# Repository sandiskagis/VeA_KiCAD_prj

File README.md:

# VeA_KiCAD_prj
Šī repozitorija paredzēta kursa projektiem

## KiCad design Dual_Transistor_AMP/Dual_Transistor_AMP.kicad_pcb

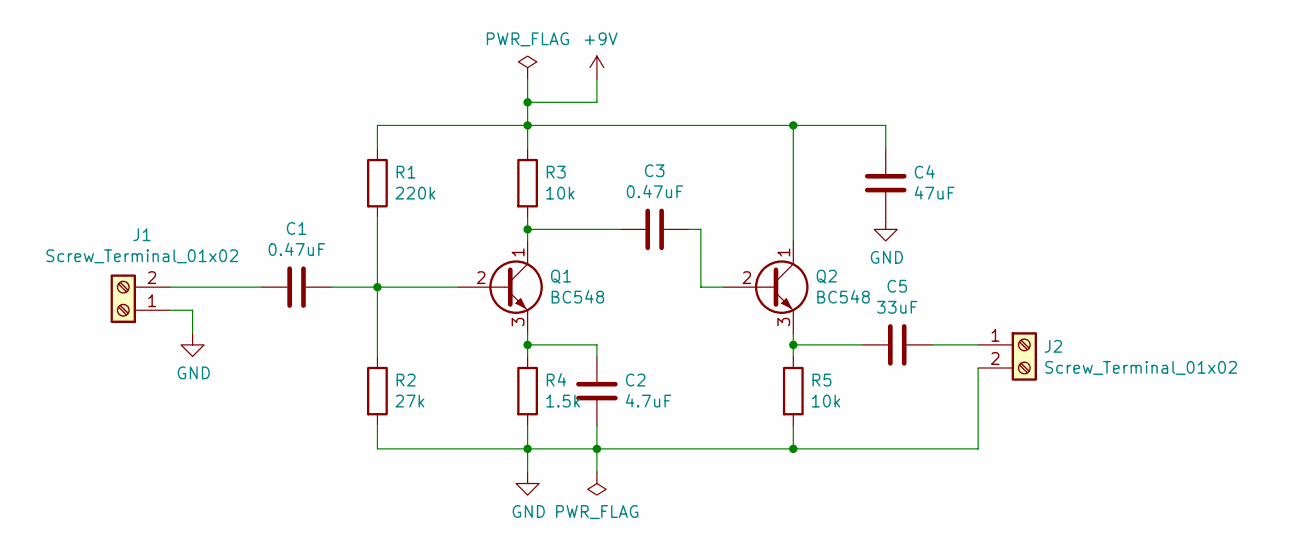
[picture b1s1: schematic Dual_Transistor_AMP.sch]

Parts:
C1, C3: 0.47uF; C_0402_1005Metric
C2: 4.7uF; C_1210_3225Metric
C4: 47uF; C_2220_5650Metric
C5: 33uF; C_0805_2012Metric
J1, J2: Screw_Terminal_01x02; TerminalBlock_4Ucon_1x02_P3.50mm_Horizontal
Q1, Q2: BC548; TO-92_Inline
R1: 220k; R_0402_1005Metric
R2: 27k; R_0402_1005Metric
R3, R5: 10k; R_0402_1005Metric
R4: 1.5k; R_0402_1005Metric

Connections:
+9V: C4.1, Q2.1 (C), R1.1, R3.1; also elsewhere on the board
GND: C2.2, C4.2, J1.1, J2.2, R2.2, R4.2, R5.2; also elsewhere on the board
unnamed: C1.1, Q1.2 (B), R1.2, R2.1
unnamed: C1.2, J1.2
unnamed: C2.1, Q1.3 (E), R4.1
unnamed: C3.1, Q2.2 (B)
unnamed: C3.2, Q1.1 (C), R3.2
unnamed: C5.1, J2.1
unnamed: C5.2, Q2.3 (E), R5.1

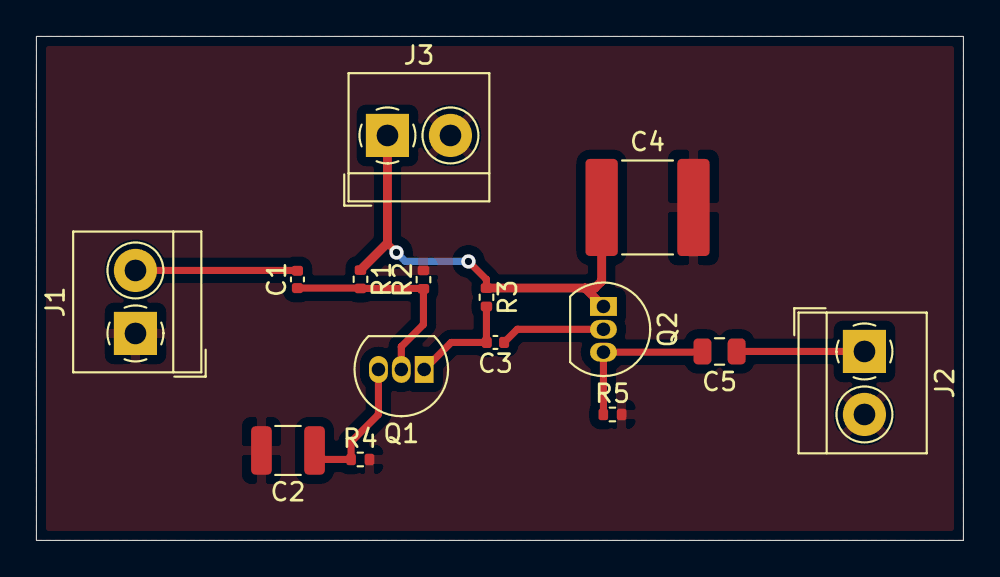
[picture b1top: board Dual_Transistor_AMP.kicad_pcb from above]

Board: 2 copper layers, 51.5 x 28.0 mm, 15 parts (0 on the bottom side), 9 nets.

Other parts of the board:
J3: Screw_Terminal_01x02; TerminalBlock_4Ucon_1x02_P3.50mm_Horizontal

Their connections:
+9V: J3.1; also elsewhere on the board
GND: J3.2; also elsewhere on the board

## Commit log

2021-10-13 MultiVib
2021-10-19 Add files via upload
    POWER_SUPPLY
2021-10-26 Single_transistor_AMP
